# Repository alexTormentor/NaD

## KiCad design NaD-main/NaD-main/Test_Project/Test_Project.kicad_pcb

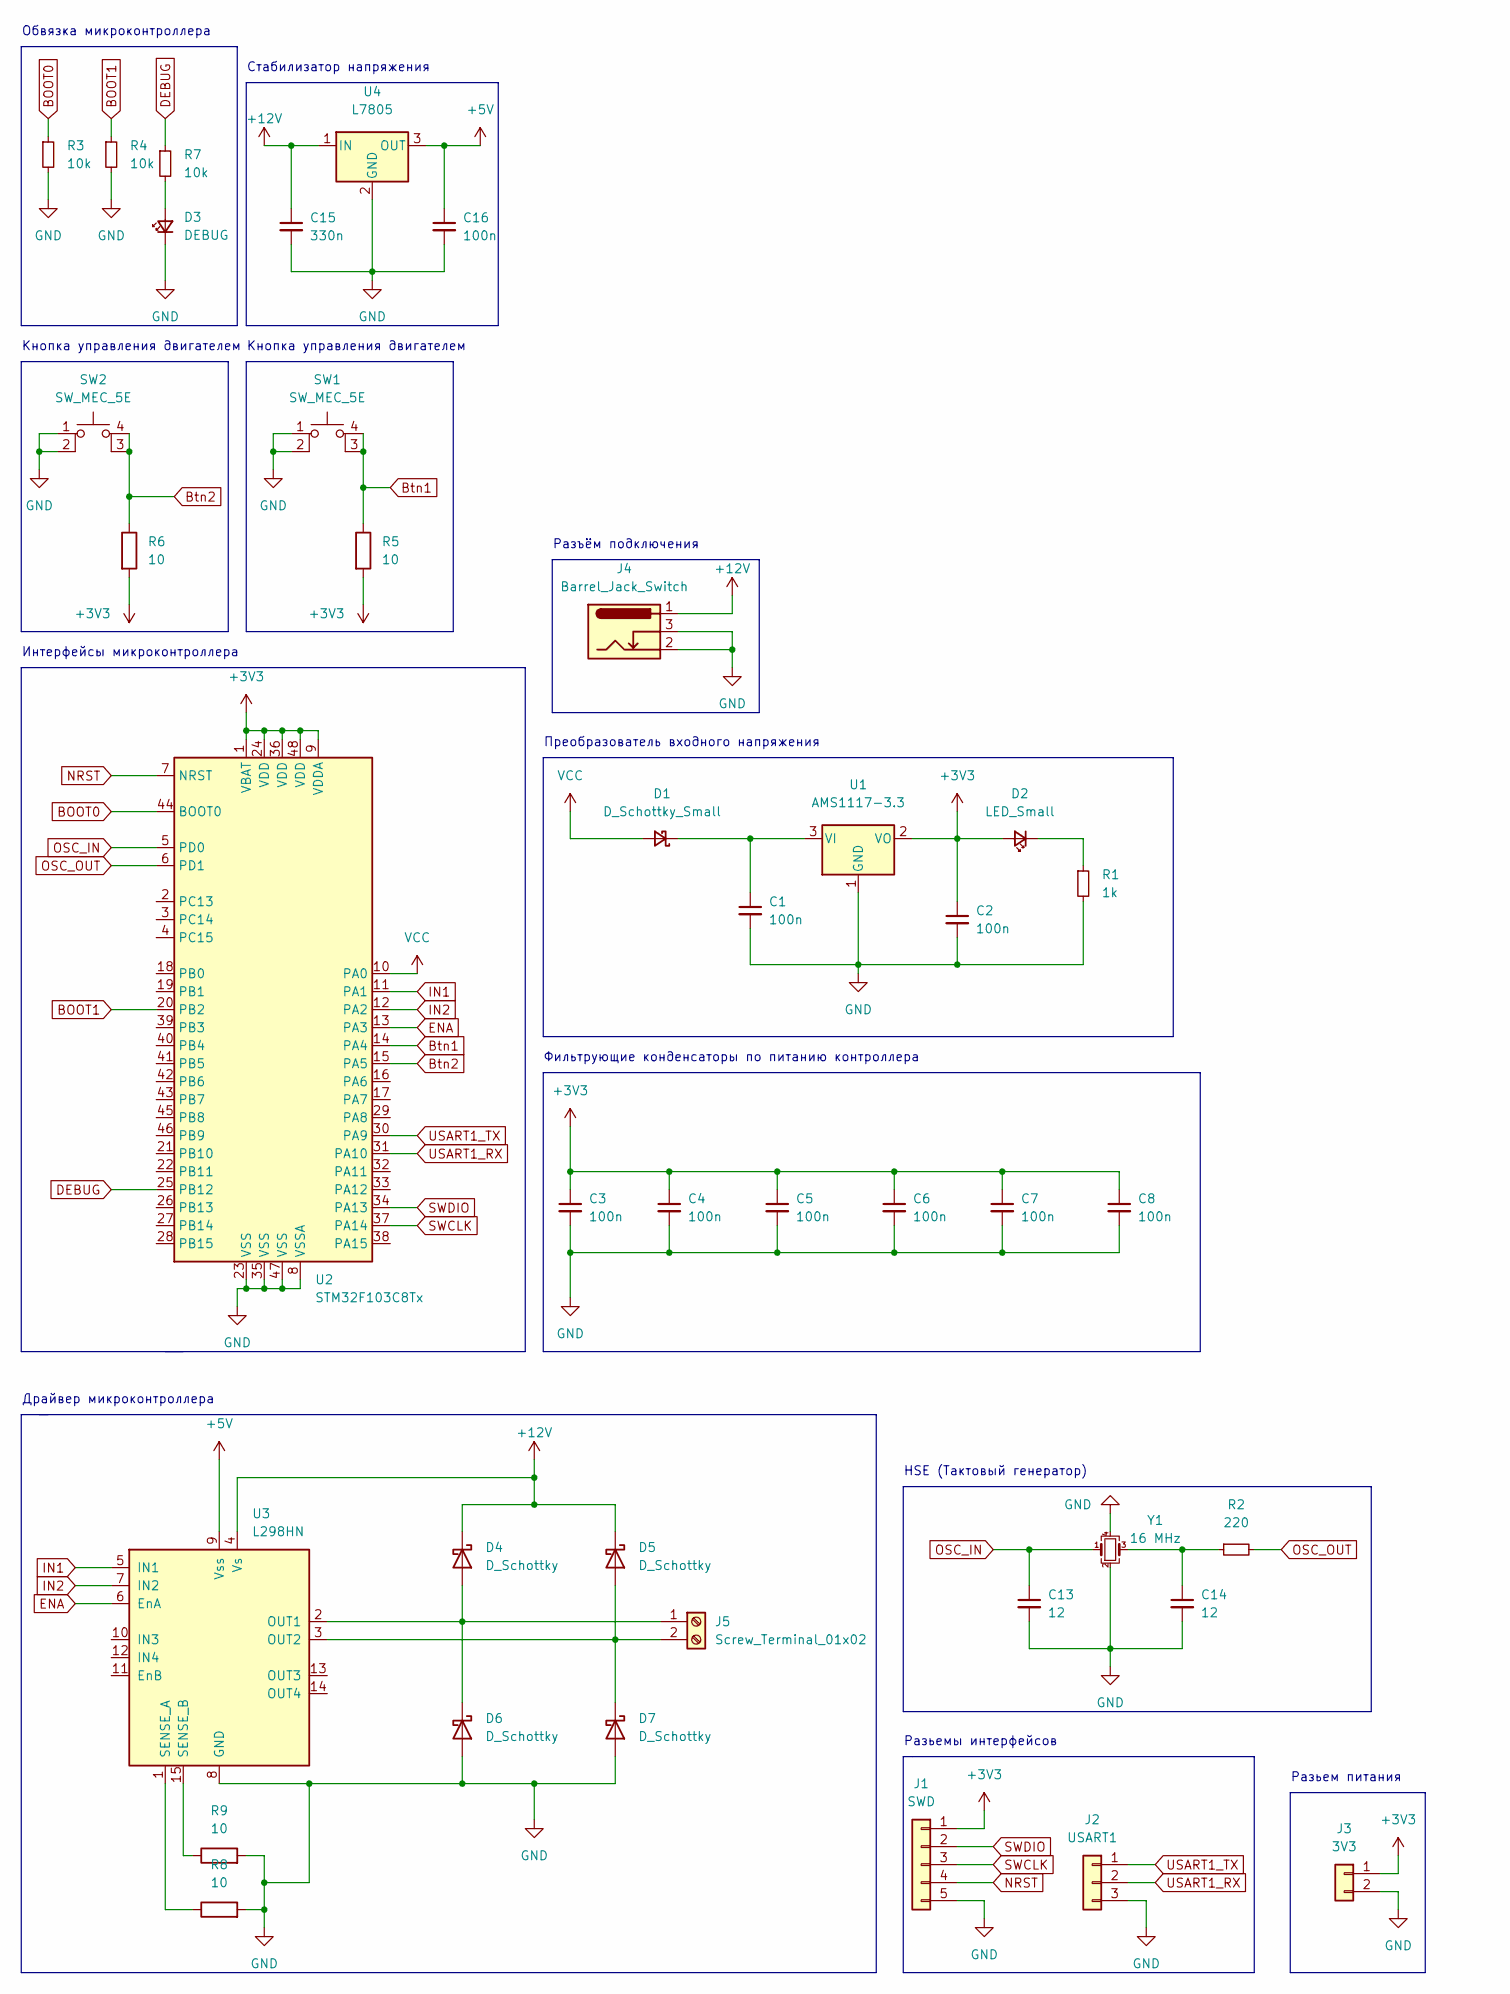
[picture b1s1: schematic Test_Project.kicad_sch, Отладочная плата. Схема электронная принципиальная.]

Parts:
C1, C2, C16: 100n; CP_Radial_D6.3mm_P2.50mm
C3, C4, C5, C6, C7, C8: 100n; C_0805_2012Metric
C13, C14: 12; C_0805_2012Metric
C15: 330n; CP_Radial_D6.3mm_P2.50mm
D1: D_Schottky_Small; D_0805_2012Metric
D2: LED_Small; LED_0805_2012Metric
D3: DEBUG; LED_0805_2012Metric
D4, D5, D6, D7: D_Schottky; D_SMA
J1: SWD; PinHeader_1x05_P2.54mm_Vertical
J2: USART1; PinSocket_1x03_P2.54mm_Vertical
J3: 3V3; PinSocket_1x02_P2.54mm_Vertical
J4: Barrel_Jack_Switch; BarrelJack_GCT_DCJ200-10-A_Horizontal
J5: Screw_Terminal_01x02; TerminalBlock_bornier-2_P5.08mm
R1: 1k; R_0805_2012Metric
R2: 220; R_0805_2012Metric
R3, R4, R7: 10k; R_0805_2012Metric
R5, R6, R8, R9: 10; R_0805_2012Metric
SW1, SW2: SW_MEC_5E; SW_PUSH_6mm
U1: AMS1117-3.3; SOT-223-3_TabPin2
U2: STM32F103C8Tx; LQFP-48_7x7mm_P0.5mm
U3: L298HN; TO-220-15_P2.54x2.54mm_StaggerOdd_Lead4.58mm_Vertical
U4: L7805; TO-220-3_Vertical
Y1: 16 MHz; Crystal_SMD_3225-4Pin_3.2x2.5mm

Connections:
+3V3: C2.1, C3.1, C4.1, C5.1, C6.1, C7.1, C8.1, D2.2 (A), J1.1, J3.1, R5.2, R6.2, U1.2 (VO), U2.1 (VBAT), U2.9 (VDDA), U2.24 (VDD), U2.36 (VDD), U2.48 (VDD)
+5V: C16.1, U3.9 (Vss), U4.3 (OUT)
+12V: C15.1, D4.1 (K), D5.1 (K), J4.1, U3.4 (Vs), U4.1 (IN)
BOOT0: R3.1, U2.44 (BOOT0)
BOOT1: R4.1, U2.20 (PB2)
Btn1: R5.1, SW1.3 (K), SW1.4 (A), U2.14 (PA4)
Btn2: R6.1, SW2.3 (K), SW2.4 (A), U2.15 (PA5)
DEBUG: R7.1, U2.25 (PB12)
ENA: U2.13 (PA3), U3.6 (EnA)
GND: C1.2, C2.2, C3.2, C4.2, C5.2, C6.2, C7.2, C8.2, C13.2, C14.2, C15.2, C16.2, D3.1 (K), D6.2 (A), D7.2 (A), J1.5, J2.3, J3.2, J4.2, J4.3, R1.2, R3.2, R4.2, R8.2, R9.2, SW1.1, SW1.2, SW2.1, SW2.2, U1.1 (GND), U2.8 (VSSA), U2.23 (VSS), U2.35 (VSS), U2.47 (VSS), U3.8 (GND), U4.2 (GND), Y1.2, Y1.4
IN1: U2.11 (PA1), U3.5 (IN1)
IN2: U2.12 (PA2), U3.7 (IN2)
NRST: J1.4, U2.7 (NRST)
unnamed: C1.1, D1.1 (K), U1.3 (VI)
unnamed: C14.1, R2.1, Y1.3
unnamed: D2.1 (K), R1.1
unnamed: D3.2 (A), R7.2
unnamed: D4.2 (A), D6.1 (K), J5.1, U3.2 (OUT1)
unnamed: D5.2 (A), D7.1 (K), J5.2, U3.3 (OUT2)
unnamed: R8.1, U3.1 (SENSE_A)
unnamed: R9.1, U3.15 (SENSE_B)
OSC_IN: C13.1, U2.5 (PD0), Y1.1
OSC_OUT: R2.2, U2.6 (PD1)
SWCLK: J1.3, U2.37 (PA14)
SWDIO: J1.2, U2.34 (PA13)
USART1_RX: J2.2, U2.31 (PA10)
USART1_TX: J2.1, U2.30 (PA9)
VCC: D1.2 (A), U2.10 (PA0)

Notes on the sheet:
Интерфейсы микроконтроллера
Кнопка управления двигателем
Стабилизатор напряжения
Разьемы интерфейсов
Разъём подключения
HSE (Тактовый генератор)
Обвязка микроконтроллера
Фильтрующие конденсаторы по питанию контроллера
Драйвер микроконтроллера
Преобразователь входного напряжения
Разьем питания

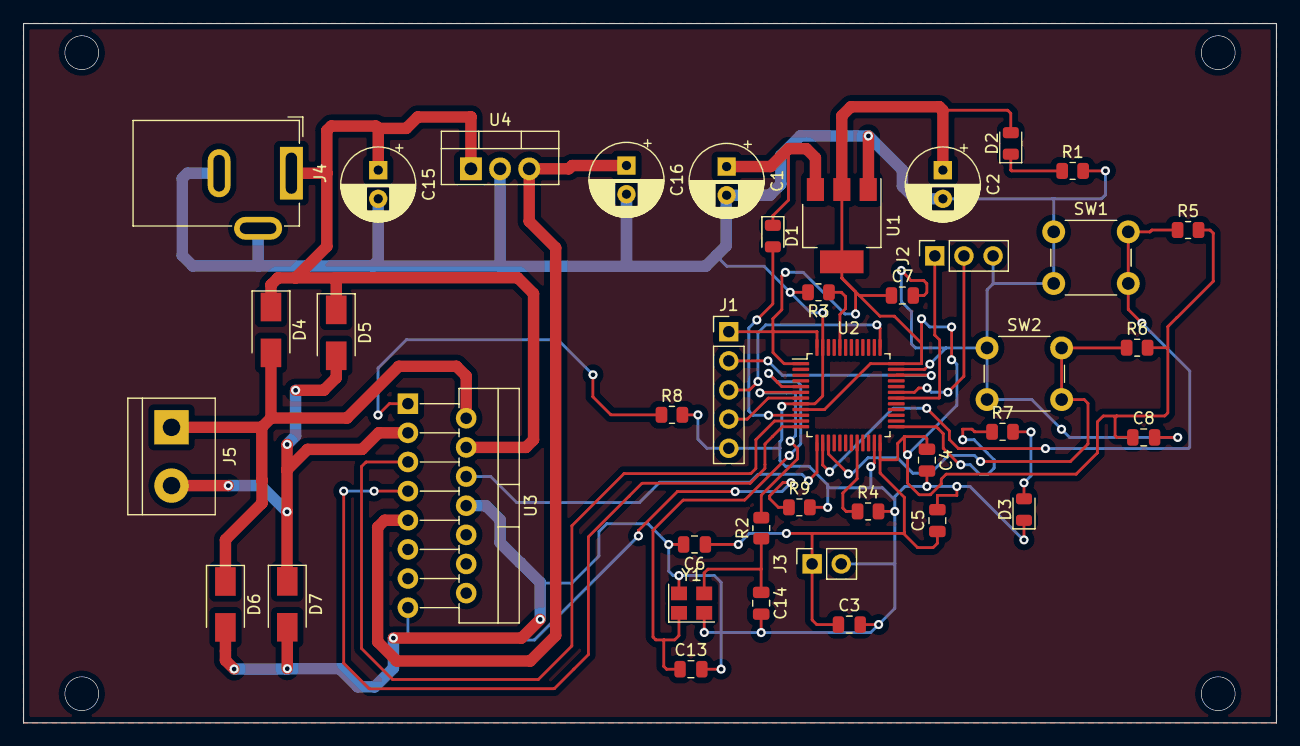
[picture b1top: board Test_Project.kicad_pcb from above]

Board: 2 copper layers, 109.2 x 61.0 mm, 40 parts (0 on the bottom side), 28 nets.

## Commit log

2022-11-08 курсач
2022-11-21 added buttons to scheme
2022-12-06 Documentation
